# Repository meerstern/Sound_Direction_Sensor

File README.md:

#  音方位センサ基板
# Sound_Direction_Sensor
This board detects the direction of sound with 4-pdm mems mic using GCC-PHAT algorithm.

## 概要
  * 音の時間差から計算して8つのLED及びI2C、UARTで結果(角度)を出力する基板です  
  * 4つのPDMデジタルマイクSPH0641LMおよびSTM32F411RCを搭載しています  
  * GCC-PHAT(Generalized Cross-Correlation. PHAse Transform)方式です  
  * 数kHz前後の音をフィルタして音の時間差から方位を検出します  
  * 誤検知を低減するために、音変化（標準偏差）が大きい場合に角度出力します  
  * 音変化（標準偏差）の閾値は基板上の可変抵抗もしくはコマンドから変更できます  
  * 人の声やリズム音等の方位検出に向いています  
  * 手やモノを叩く音等の瞬間的な音の場合、反射等の影響が大きく誤検知しやすくなります  
  
## 仕様
  * 角度分解能は約22.5度～30度程度(音源や環境、処理に依存)
  * 方位LED 8つ搭載
  * 1秒間に約5~6回測定し、結果を出力します  
  * 36kHzサンプリング
  * 電源3.3~5V、UARTもしくはI2C(5V耐圧)
  * I2CはGrove互換コネクタ搭載、UARTは基板上ピンヘッダから接続  
  * UARTボーレート9600bps、データサイズ8bit、パリティ無、ストップ1bitが既定値です  
  * 起動直後にのみ基板上の可変抵抗を読み取り、音変化（標準偏差）の閾値として設定します  
  * I2CもしくはUARTから音変化（標準偏差）閾値を上書き設定できます  
  * リセットや電源再投入で音変化（標準偏差）閾値は消去され、保持されません(可変抵抗値が再度反映)  
  * 電源投入後、自動的に方位検知を開始するため、電源供給のみで方位検知可能です  

## 外形
  * 40mm円形基板(コネクタ含まず)
  * マイク距離36mm円形
  * M2穴x3 穴間隔横および縦 24.3mm
  
## アプリケーション例
  * 音源の方向を向く小型の首振りロボット  
  * 声でカメラの向きを動かして撮影するカメラステージ
   
## 注意点
  * 厳密な角度検出が必要な用途には向いていません  
  * 音の反射やサンプリングタイミングによって誤検知する場合があります  
  * 騒音環境下、衝撃/振動環境下の用途には向いていません  
  * 5cm程度～1m程度の音の方位の検出を想定しています  
  * 数m以上の遠方からの音の場合、反射等の影響で誤検知の可能性が高くなります  
  * 頻繁に方位LEDが点灯する場合や誤検知が多発する場合は音変化閾値を上げてください  
  * 場合によって起動直後数秒間はソフトフィルタ処理の影響で方位検出が安定しない場合があります  
  * Groveケーブルは同梱されていません 別途ご用意ください   

## 閾値調整目安
  * 音源がない環境下での音変化値Actに対して閾値を1.2~1.5倍程度の値に設定してください  
  * 誤検知が多い場合は環境に応じて閾値を音変化値Actに対してより高く設定してください  
  　例　静かな状態で音変化0.8前後の場合、音変化閾値を1.2程度に設定  
   
## UART通信 
  * 起動直後はファームのバージョンおよびビルド日時、音変化の閾値が出力されます  
  * 1秒間に約5~6回、検出角度Deg、フィルタ前角度DegOrg、音変化値Actが出力されます  
  * 音変化閾値以下は未検出として-1度を出力します  
  * act=XX.XX(Enterキー)で音変換閾値を変更できます  
  * act?(Enterキー)で現状の音変換閾値を確認できます  
  * rst!(Enterキー)でソフトウェアリセットさせることができます 
  * 下記の例では音変換閾値1.0のため、1.0を超えて音変換値1.6の4つ目が206.6度として検出  
    
	Sound Direction Sensor vX.X (ビルド日時)[\r\n]  
	Activity Threshold: 1.0[\r\n]  
	Deg:-1.0,        DegOrg:201.8,   Act:0.69,[\r\n]  
	Deg:-1.0,        DegOrg:0.0,     Act:0.71,[\r\n]  
	Deg:-1.0,        DegOrg:90.0,    Act:0.73,[\r\n]  
	Deg:206.6,       DegOrg:206.6,   Act:1.60,[\r\n]  
	Deg:-1.0,        DegOrg:90.0,    Act:0.73,[\r\n]  

| コマンド名 | コマンド | 引数 | 例 | 
|:-----------|:------------|:------------|:------------|
| 音変換閾値設定 | act= | 小数設定値 | act=1.2(Enterキー) |
| 音変換閾値確認 | act? | なし | act?(Enterキー) |
| リセット |	rst! | なし | rst!(Enterキー) | 

## I2C通信
　 * I2Cデバイスアドレスは0x60(8bitアドレス)、0x30(7bitアドレス)です  
  * 角度および音変化値は10倍の整数値がレジスタに格納されています  
  * 必要に応じてマスタ側で0.1を乗算し、角度等に変換してください  
  * 書き込み時についても同様に設定したい閾値の10倍の整数値を書き込んでください  
    
  * 読み込み
  
| レジスタ名 | オフセット | 詳細 | 
|:-----------|:------------|:------------|
| 角度H(フィルタ後) |0x00 | 角度HighByte | 
| 角度L(フィルタ後) |0x01 | 角度LowByte | 
| 角度H(フィルタ前) |0x02 | 角度HighByte | 
| 角度L(フィルタ前) |0x03 | 角度LowByte | 
| 音変化値H |0x04 | 観測値HighByte | 
| 音変換値L |0x05 | 観測値LowByte | 
| 更新フラグ |0x06 | 値更新0x01 | 
| デバイスID |0x07 | 0x43固定値 | 

  * 書き込み  
  
| レジスタ名 | オフセット | 引数 | 
|:-----------|:------------|:------------|
| 音変換閾値H |0x04 | 設定値HighByte | 
| 音変換閾値L |0x05 | 設定値LowByte | 

※オフセット0x04で設定値のHighByteとLowByteの2バイトを一度で書き込んでください  
(スレーブアドレス)+(オフセット)+(設定値2Byte)  

## 販売サイト
  * [スイッチサイエンス][2]

[2]: https://www.switch-science.com/products/8129

https://youtu.be/5QTcDwFN5Rs

https://youtu.be/rlhwlwNsYnQ

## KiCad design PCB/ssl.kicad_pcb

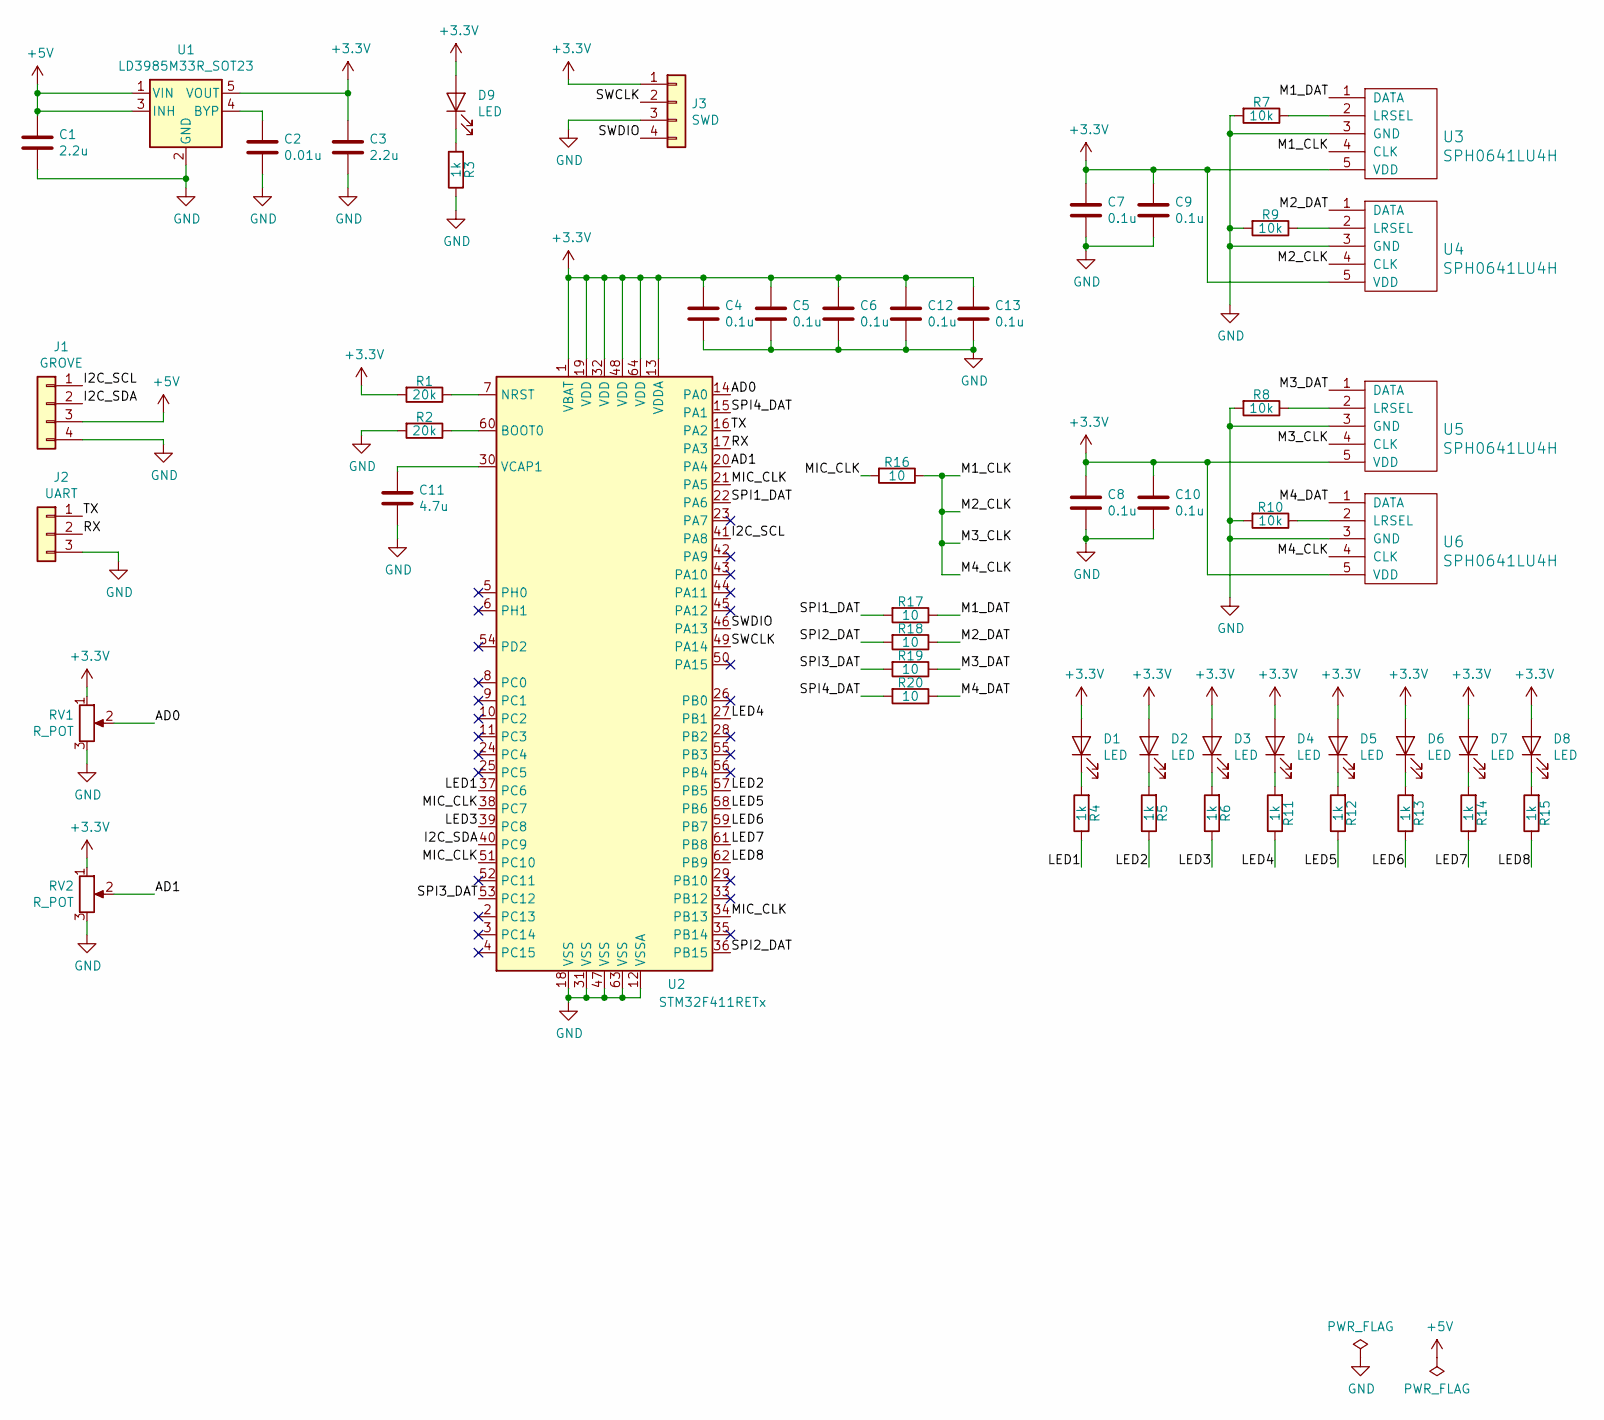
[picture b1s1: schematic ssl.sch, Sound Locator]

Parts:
C1, C3: 2.2u; C_0805_2012Metric
C2: 0.01u; C_0603_1608Metric
C4, C5, C6, C7, C8, C9, C10, C12, C13: 0.1u; C_0603_1608Metric
C11: 4.7u; C_0805_2012Metric
D1, D2, D3, D4, D5, D6, D7, D8, D9: LED; D_0603_1608Metric
J1: GROVE
J2: UART; PinHeader_1x03_P2.54mm_Vertical
J3: SWD; PinHeader_1x04_P2.54mm_Vertical
R1, R2: 20k; R_0603_1608Metric
R3, R4, R5, R6, R11, R12, R13, R14, R15: 1k; R_0603_1608Metric
R7, R8, R9, R10: 10k; R_0603_1608Metric
R16, R17, R18, R19, R20: 10; R_0603_1608Metric
RV1, RV2: R_POT; rcl-RTRIMCVR42A
U1: LD3985M33R_SOT23; SOT-23-5
U2: STM32F411RETx; LQFP-64_10x10mm_P0.5mm
U3, U4, U5, U6: SPH0641LU4H

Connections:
+3V3: C3.1, C4.1, C5.1, C6.1, C7.1, C8.1, C9.1, C10.1, C12.1, C13.1, D1.2 (A), D2.2 (A), D3.2 (A), D4.2 (A), D5.2 (A), D6.2 (A), D7.2 (A), D8.2 (A), D9.2 (A), J3.1, R1.2, RV1.1, RV2.1, U1.5 (VOUT), U2.1 (VBAT), U2.13 (VDDA), U2.19 (VDD), U2.32 (VDD), U2.48 (VDD), U2.64 (VDD), U3.5 (VDD), U4.5 (VDD), U5.5 (VDD), U6.5 (VDD)
+5V: C1.1, J1.3, U1.1 (VIN), U1.3 (INH)
/AD0: RV1.2, U2.14 (PA0)
/AD1: RV2.2, U2.20 (PA4)
/I2C_SCL: J1.1, U2.41 (PA8)
/I2C_SDA: J1.2, U2.40 (PC9)
/LED1: R4.1, U2.37 (PC6)
/LED2: R5.1, U2.57 (PB5)
/LED3: R6.1, U2.39 (PC8)
/LED4: R11.1, U2.27 (PB1)
/LED5: R12.1, U2.58 (PB6)
/LED6: R13.1, U2.59 (PB7)
/LED7: R14.1, U2.61 (PB8)
/LED8: R15.1, U2.62 (PB9)
/M1_CLK: R16.1, U3.4 (CLK), U4.4 (CLK), U5.4 (CLK), U6.4 (CLK)
/M1_DAT: R17.1, U3.1 (DATA)
/M2_DAT: R18.1, U4.1 (DATA)
/M3_DAT: R19.1, U5.1 (DATA)
/M4_DAT: R20.1, U6.1 (DATA)
/MIC_CLK: R16.2, U2.21 (PA5), U2.34 (PB13), U2.38 (PC7), U2.51 (PC10)
/RX: J2.2, U2.17 (PA3)
/SPI1_DAT: R17.2, U2.22 (PA6)
/SPI2_DAT: R18.2, U2.36 (PB15)
/SPI3_DAT: R19.2, U2.53 (PC12)
/SPI4_DAT: R20.2, U2.15 (PA1)
/SWCLK: J3.2, U2.49 (PA14)
/SWDIO: J3.4, U2.46 (PA13)
/TX: J2.1, U2.16 (PA2)
GND: C1.2, C2.2, C3.2, C4.2, C5.2, C6.2, C7.2, C8.2, C9.2, C10.2, C11.2, C12.2, C13.2, J1.4, J2.3, J3.3, R2.2, R3.1, R7.2, R8.2, R9.2, R10.2, RV1.3, RV2.3, U1.2 (GND), U2.12 (VSSA), U2.18 (VSS), U2.31 (VSS), U2.47 (VSS), U2.63 (VSS), U3.3 (GND), U4.3 (GND), U5.3 (GND), U6.3 (GND)
unnamed: C2.1, U1.4 (BYP)
unnamed: C11.1, U2.30 (VCAP1)
unnamed: D1.1 (K), R4.2
unnamed: D2.1 (K), R5.2
unnamed: D3.1 (K), R6.2
unnamed: D4.1 (K), R11.2
unnamed: D5.1 (K), R12.2
unnamed: D6.1 (K), R13.2
unnamed: D7.1 (K), R14.2
unnamed: D8.1 (K), R15.2
unnamed: D9.1 (K), R3.2
unnamed: R1.1, U2.7 (NRST)
unnamed: R2.1, U2.60 (BOOT0)
unnamed: R7.1, U3.2 (LRSEL)
unnamed: R8.1, U5.2 (LRSEL)
unnamed: R9.1, U4.2 (LRSEL)
unnamed: R10.1, U6.2 (LRSEL)

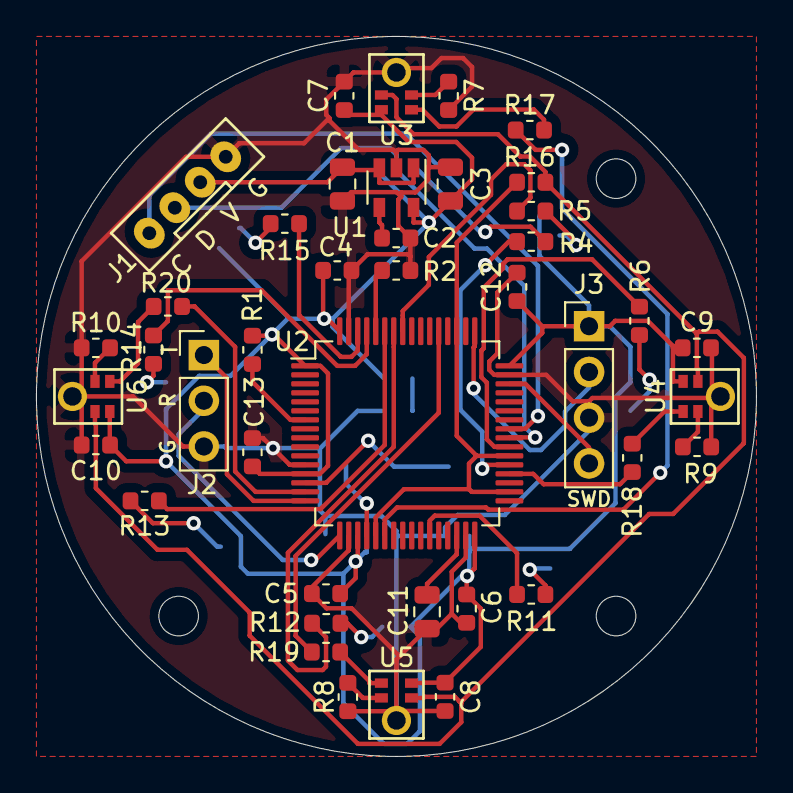
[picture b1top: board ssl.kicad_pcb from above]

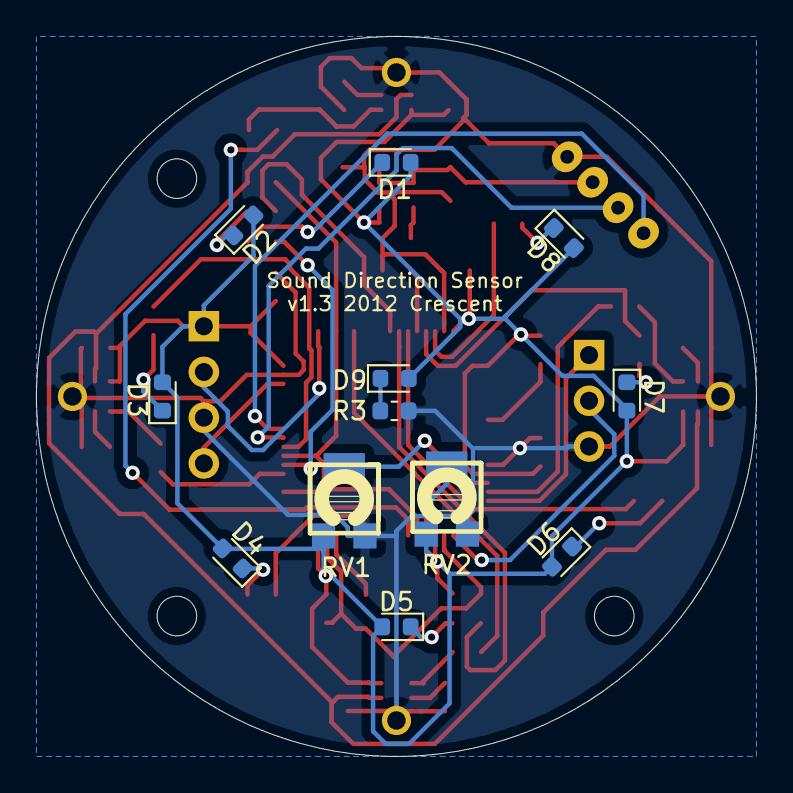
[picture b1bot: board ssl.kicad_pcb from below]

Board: 2 copper layers, 40.0 x 40.0 mm, 56 parts (12 on the bottom side), 46 nets.

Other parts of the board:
REF1, REF2, REF3: MountingHole_2.2mm_M2

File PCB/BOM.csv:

Elecrow PN,Parts,Value,Package,QTY,Digikey/Mouser/Manufacturer Part,Remark/ Link
,"RV2,RV1",R_POT,rcl-RTRIMCVR42A,2,652-TC33X-2-103E ,
,U2,STM32F411RETx,LQFP-64_10x10mm_P0.5mm,1,STM32F411RCT6,
C14663,"C13,C12,C10,C9,C8,C7,C6,C5,C4",0.1u,C_0603_1608Metric,9,,
2014547A,C11,4.7u,C_0805_2012Metric,1,,
,"U6,U5,U4,U3",SPH0641L,SPH0641L,4,721-SPH0641LM4H1 ,
,U1,LD3985M33R_SOT23,SOT-23-5,1,511-LD3985M33R,
C21190,"R15,R14,R13,R12,R11,R6,R5,R4,R3",1k,R_0603_1608Metric,9,,
C25804,"R10,R9,R8,R7",10k,R_0603_1608Metric,4,,
C4184,"R2,R1",20k,R_0603_1608Metric,2,,
,J1,GROVE,GROVE,1,713-110990037,
4040806A,"D8,D7,D6,D5,D4,D3,D2,D1",LED,D_0603_1608Metric,8,,
4040706A,D9,LED,D_0603_1608Metric,1,,
2014210A,"C3,C1",10u,C_0805_2012Metric,2,,
C57112,C2,0.01u,C_0603_1608Metric,1,,
C22859,"R16,R17,R18,R19,R20",10,R_0603_1608Metric,5,,

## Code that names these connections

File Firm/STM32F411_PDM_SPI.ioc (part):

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Mcu.Name=STM32F411R(C-E)Tx
Mcu.Package=LQFP64
Mcu.UserName=STM32F411RETx
PA0-WKUP.Signal=ADCx_IN0
PA1.Mode=RX_Only_Simplex_Unidirect_Slave
PA1.Signal=SPI4_MOSI
PA13.GPIOParameters=GPIO_Label
PA13.GPIO_Label=TMS
PA13.Mode=Serial_Wire
PA13.Signal=SYS_JTMS-SWDIO
PA14.GPIOParameters=GPIO_Label
PA14.GPIO_Label=TCK
PA14.Mode=Serial_Wire
PA14.Signal=SYS_JTCK-SWCLK
PA2.GPIOParameters=GPIO_Label
PA2.GPIO_Label=USART_TX
PA2.Mode=Asynchronous
PA2.Signal=USART2_TX
PA3.GPIOParameters=GPIO_Label
PA3.GPIO_Label=USART_RX
PA3.Mode=Asynchronous
PA3.Signal=USART2_RX
PA4.Signal=ADCx_IN4
PA5.Mode=RX_Only_Simplex_Unidirect_Master
PA5.Signal=SPI1_SCK
PA6.Mode=RX_Only_Simplex_Unidirect_Master
PA6.Signal=SPI1_MISO
PA8.Mode=I2C
PA8.Signal=I2C3_SCL
PB1.Signal=S_TIM3_CH4
PB13.Mode=RX_Only_Simplex_Unidirect_Slave
PB13.Signal=SPI4_SCK
PB15.Mode=RX_Only_Simplex_Unidirect_Slave
PB15.Signal=SPI2_MOSI
PB3.GPIOParameters=GPIO_Label
PB3.GPIO_Label=SWO
PB3.Signal=SYS_JTDO-SWO
PB5.Signal=S_TIM3_CH2
PB6.Signal=S_TIM4_CH1
PB7.Signal=S_TIM4_CH2
PB8.Signal=S_TIM4_CH3
PB9.Signal=S_TIM4_CH4
PC10.Mode=RX_Only_Simplex_Unidirect_Slave
PC10.Signal=SPI3_SCK
PC12.Mode=RX_Only_Simplex_Unidirect_Slave
PC12.Signal=SPI3_MOSI
PC13-ANTI_TAMP.GPIOParameters=GPIO_Label,GPIO_ModeDefaultEXTI
PC13-ANTI_TAMP.GPIO_Label=B1 [Blue PushButton]
PC13-ANTI_TAMP.GPIO_ModeDefaultEXTI=GPIO_MODE_IT_FALLING
PC13-ANTI_TAMP.Signal=GPXTI13
PC14-OSC32_IN.Signal=RCC_OSC32_IN
PC15-OSC32_OUT.Signal=RCC_OSC32_OUT
PC6.Signal=S_TIM3_CH1
PC7.Mode=RX_Only_Simplex_Unidirect_Slave
PC7.Signal=SPI2_SCK
PC8.Signal=S_TIM3_CH3
PC9.Mode=I2C
PC9.Signal=I2C3_SDA
PH0\ -\ OSC_IN.Signal=RCC_OSC_IN
PH1\ -\ OSC_OUT.Signal=RCC_OSC_OUT
RCC.HSE_VALUE=8000000
RCC.SYSCLKFreq_VALUE=100000000
RCC.SYSCLKSource=RCC_SYSCLKSOURCE_PLLCLK
board=NUCLEO-F411RE
boardIOC=true

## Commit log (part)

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2022-03-21 Add images
2022-03-21 Add PCB Data
2022-03-23 Add figures
2022-03-23 Add Firm
2022-03-23 Add Files
2022-04-22 Add sample code
